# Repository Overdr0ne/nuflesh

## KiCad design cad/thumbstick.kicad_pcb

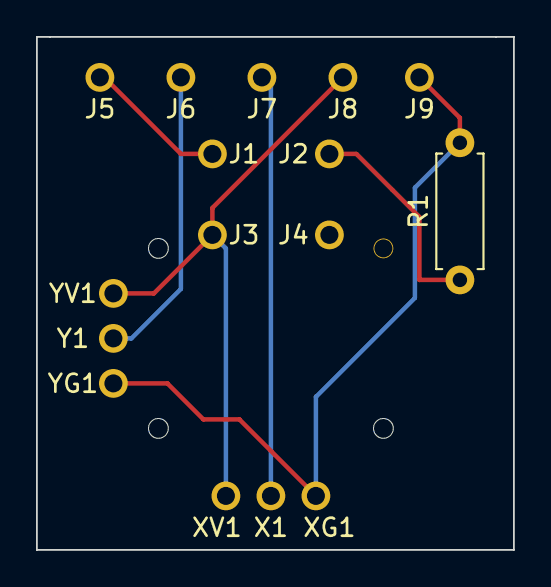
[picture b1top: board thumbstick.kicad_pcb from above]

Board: 2 copper layers, 26.5 x 28.5 mm, 16 parts (0 on the bottom side), 6 nets.

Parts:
J1, J2, J3, J4, J5, J6, J7, J8, J9: CONN_01X01_MALE; SolderWirePad_single_1mmDrill
R1: R; R_Axial_DIN0207_L6.3mm_D2.5mm_P7.62mm_Horizontal
X1: CONN_01X01_MALE; SolderWirePad_single_1mmDrill
XG1: CONN_01X01_MALE; SolderWirePad_single_1mmDrill
XV1: CONN_01X01_MALE; SolderWirePad_single_1mmDrill
Y1: CONN_01X01_MALE; SolderWirePad_single_1mmDrill
YG1: CONN_01X01_MALE; SolderWirePad_single_1mmDrill
YV1: CONN_01X01_MALE; SolderWirePad_single_1mmDrill

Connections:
unnamed: J1.1, J5.1
unnamed: J2.1, R1.1
unnamed: J3.1, J8.1, XV1.1, YV1.1
unnamed: J6.1, Y1.1
unnamed: J7.1, X1.1
unnamed: J9.1, R1.2, XG1.1, YG1.1

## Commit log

2017-07-04 add basic gesture functionality
2017-07-25 add Arduino Makefile
2017-07-25 convert ino to cpp
2017-08-08 restructured dirs to accommodate host code
2017-08-18 add host processing of gestures
2017-08-18 codify arduino output for host gesture processing
2017-08-18 remove miscellaneous files
2017-08-20 add modifier support
2017-09-20 add mouse mode
2017-09-20 add thumbstick cad model
